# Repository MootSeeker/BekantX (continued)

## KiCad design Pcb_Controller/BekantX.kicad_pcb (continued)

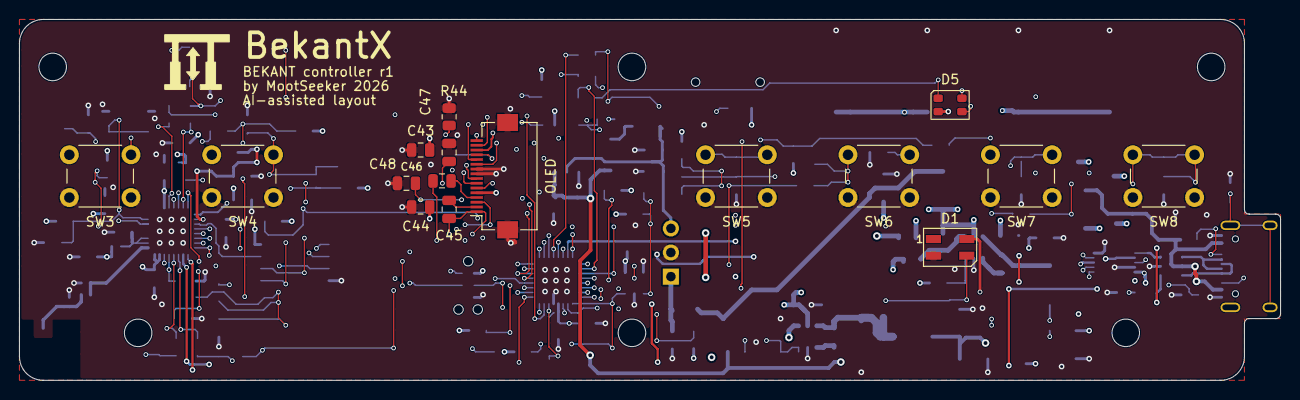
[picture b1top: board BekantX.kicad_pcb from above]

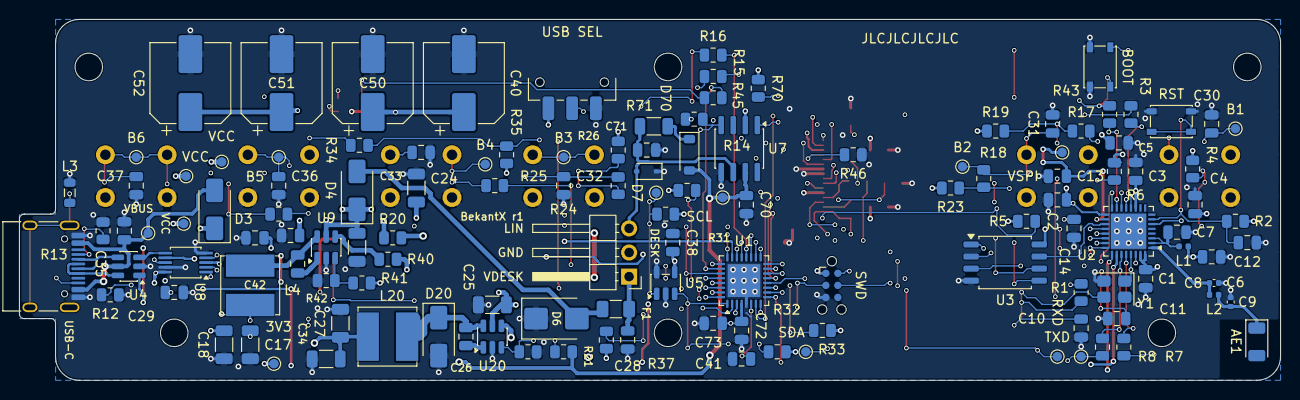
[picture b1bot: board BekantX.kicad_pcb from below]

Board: 6 copper layers, 132.8 x 38.0 mm, 151 parts (129 on the bottom side), 92 nets.

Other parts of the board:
H1, H2, H3, H4, H5, H6: M2.5 hole 2.9 mm; MountingHole_2.9mm_NPTH

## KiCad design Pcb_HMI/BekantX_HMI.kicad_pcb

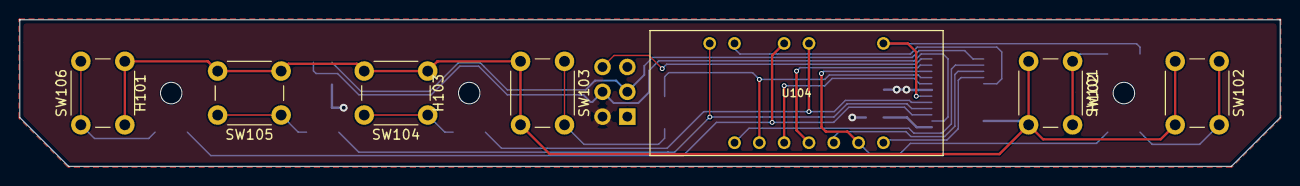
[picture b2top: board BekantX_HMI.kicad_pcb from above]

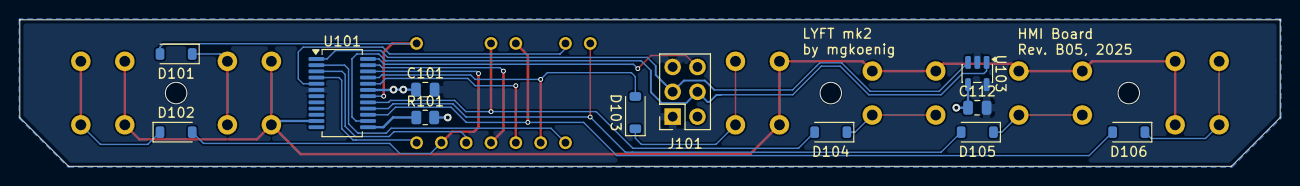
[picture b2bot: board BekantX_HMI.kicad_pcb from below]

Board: 2 copper layers, 129.0 x 15.0 mm, 22 parts (12 on the bottom side), 19 nets.

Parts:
C101: 10u; C_0805_2012Metric
C112: 100n; C_0805_2012Metric
D101, D102, D103, D104, D105, D106: 1N4148W; D_SOD-123
H101, H102, H103: MountingHole; MountingHole_2.2mm_M2
J101: Conn_HMI; PinSocket_2x03_P2.54mm_Vertical
R101: 13k; R_0805_2012Metric
SW101, SW102, SW103, SW104, SW105, SW106: SW_Omron_B3FS; SW_PUSH_6mm
U101: AS1115-BSST; QSOP-24_3.9x8.7mm_P0.635mm
U103: 24FC01T; SOT-23-5
U104: HDSP-433G

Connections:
+3V3: C101.1, C112.1, J101.2, R101.2, U101.19 (VDD), U103.4 (VCC)
GND: C101.2, C112.2, J101.1, J101.5, U101.6 (GND), U103.2 (GND), U103.5 (WP)
HMI_IRQ: J101.6, U101.24 (IRQ)
I2C_SCL: J101.4, U101.14 (SCL), U103.1 (SCL)
I2C_SDA: J101.3, U101.1 (SDA), U103.3 (SDA)
KEY_A: SW101.2, SW102.2, SW103.2, SW104.2, SW105.2, SW106.2, U101.11 (KEYA)
unnamed: D101.1 (K), SW101.1
unnamed: D102.1 (K), SW102.1
unnamed: D103.1 (K), SW103.1
unnamed: D104.1 (K), SW104.1
unnamed: D105.1 (K), SW105.1
unnamed: D106.1 (K), SW106.1
unnamed: R101.1, U101.13 (ISET)
SEG_A: D106.2 (A), U101.15 (SEGA)
SEG_B: D104.2 (A), U101.17 (SEGB)
SEG_DP: D102.2 (A), U101.22 (SEGDP)
SEG_E: D103.2 (A), U101.21 (SEGE)
SEG_F: D105.2 (A), U101.16 (SEGF)
SEG_G: D101.2 (A), U101.18 (SEGG)

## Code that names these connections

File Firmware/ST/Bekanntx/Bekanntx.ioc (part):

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Mcu.Name=STM32G0B1K(B-C-E)Ux
Mcu.Package=UFQFPN32
Mcu.UserName=STM32G0B1KBUx
PA0.Mode=TX_Only_Simplex_Unidirect_Master
PA0.Signal=SPI2_SCK
PA1.GPIOParameters=GPIO_Label
PA1.GPIO_Label=DISP_CS
PA1.Signal=GPIO_Output
PA10.Mode=TX_Only_Simplex_Unidirect_Master
PA10.Signal=SPI2_MOSI
PA11\ [PA9].Mode=Device
PA11\ [PA9].Signal=USB_DM
PA12\ [PA10].Mode=Device
PA12\ [PA10].Signal=USB_DP
PA13.Mode=Serial_Wire
PA13.Signal=SYS_SWDIO
PA14-BOOT0.Mode=Serial_Wire
PA14-BOOT0.Signal=SYS_SWCLK
PA15.Signal=S_TIM2_CH1_ETR
PA2.Mode=Multiprocessor_communication
PA2.Signal=LPUART1_TX
PA3.Mode=Multiprocessor_communication
PA3.Signal=LPUART1_RX
PA4.Mode=NSS_Signal_Hard_Input
PA4.Signal=SPI1_NSS
PA5.Mode=Full_Duplex_Slave
PA5.Signal=SPI1_SCK
PA6.Mode=Full_Duplex_Slave
PA6.Signal=SPI1_MISO
PA7.Mode=Full_Duplex_Slave
PA7.Signal=SPI1_MOSI
PA8.GPIOParameters=GPIO_Label
PA8.GPIO_Label=DISP_DC
PA8.Signal=GPIO_Output
PA9.GPIOParameters=GPIO_Label
PA9.GPIO_Label=DISP_RES
PA9.Signal=GPIO_Output
PB0.GPIOParameters=GPIO_PuPd,GPIO_Label
PB0.GPIO_Label=BTN_2
PB0.GPIO_PuPd=GPIO_PULLUP
PB0.Signal=GPXTI0
PB1.GPIOParameters=GPIO_PuPd,GPIO_Label
PB1.GPIO_Label=BTN_1
PB1.GPIO_PuPd=GPIO_PULLUP
PB1.Signal=GPIO_Input
PB2.GPIOParameters=GPIO_PuPd,GPIO_Label
PB2.GPIO_Label=BTN_3
PB2.GPIO_PuPd=GPIO_PULLUP
PB2.Signal=GPXTI2
PB3.Signal=S_TIM2_CH2
PB4.GPIOParameters=GPIO_PuPd,GPIO_Label
PB4.GPIO_Label=BTN_4
PB4.GPIO_PuPd=GPIO_PULLUP
PB4.Signal=GPIO_Input
PB5.GPIOParameters=PinState,GPIO_Label,GPIO_ModeDefaultOutputPP
PB5.GPIO_Label=FSPI_INT
PB5.GPIO_ModeDefaultOutputPP=GPIO_MODE_OUTPUT_OD
PB5.PinState=GPIO_PIN_SET
PB5.Signal=GPIO_Output
PB6.Mode=LIN
PB6.Signal=USART1_TX
PB7.Mode=LIN
PB7.Signal=USART1_RX
PB8.Mode=I2C
PB8.Signal=I2C1_SCL
PB9.Mode=I2C
PB9.Signal=I2C1_SDA
PC14-OSC32_IN\ (PC14).GPIOParameters=GPIO_PuPd,GPIO_Label
PC14-OSC32_IN\ (PC14).GPIO_Label=BTN_5
PC14-OSC32_IN\ (PC14).GPIO_PuPd=GPIO_PULLUP
PC14-OSC32_IN\ (PC14).Signal=GPIO_Input
PC15-OSC32_OUT\ (PC15).GPIOParameters=GPIO_PuPd,GPIO_Label
PC15-OSC32_OUT\ (PC15).GPIO_Label=BTN_6
PC15-OSC32_OUT\ (PC15).GPIO_PuPd=GPIO_PULLUP
PC15-OSC32_OUT\ (PC15).Signal=GPIO_Input
PC6.Signal=S_TIM2_CH3
RCC.HSE_VALUE=8000000
RCC.SYSCLKFreq_VALUE=16000000
board=custom

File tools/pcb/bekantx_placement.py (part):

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    j10 = fixed(p["J10"], 68.6, 30.0, "B", lambda q: q.box()[2] > q.x + 8, check=False)   # moved below
    j10.put(68.6, 30.0 + (22.0 - min(j10.pad(1)[1], j10.pad(3)[1])), j10.rot)     # pads span y = 22.0 .. 27.08
    pl.keepout("B", (70.2, 20.3, 90.0, 28.8), "J10 housing and cable")
    # input protection directly at the VDESK pin, on the side away from the STM32: fuse, TVS, then D4
    inp = (67.4, 29.2, 82.0, 37.4)
    pl.auto("F1", side="B", near=(70.8, 30.6), radius=3, region=inp)
    pl.auto("C28", side="B", radius=6, region=inp)
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    inflate = lambda b, m: (b[0] - m, b[1] - m, b[2] + m, b[3] + m)

    # ------------------------------------------------------------ 12 V buck (U20) and 3.3 V buck (U9): compact loops first
    a("R22", side="B", radius=6, near={"U2_FB": pin("U20", 3)})              # feedback divider at the FB pin
    a("R21", side="B", radius=6, near={"U2_FB": pin("U20", 3)})
    a("R20", side="B", radius=8)
    # U9 (LMR51610 data sheet 8.4.1): input capacitor as close as possible to VIN/GND, both feedback resistors
    # close to FB. Placed before anything else around U9 (review 2026-11-15, Major 3 and Minor 5).
    a("C15", side="B", near={"VCC": pin("U9", 5), "GND": pin("U9", 2)}, radius=4)
    a("C49", side="B", near={"VCC": pin("U9", 5)}, radius=5)
    a("C16", side="B", radius=6)
    a("R42", side="B", near={"U9_FB": pin("U9", 3)}, radius=5)
    a("R41", side="B", near={"U9_FB": pin("U9", 3)}, radius=5)
    # D4 (VIN -> VCC) between the TVS and the regulators, right of the cable housing
    a("D4", side="B", near={"VIN": (90.5, 24.5), "VCC": (95.0, 24.5)}, radius=6)
    a("C24", side="B", near={"VCC": pin("D4", 1)})
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
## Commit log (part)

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2026-04-16 Add documentation for BekantX project including LIN protocol, requirements, and inter-controller protocol
    - Introduced `bekant-lin-protocol.md` detailing the reverse-engineered LIN protocol for the IKEA BEKANT desk, covering bus characteristics, frame model, node map, runtime payload formats, and known c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
    - Created `description.md` outlining the BekantX requirements specification, including purpose, scope, architectural requirements, functional requirements, safety and fault handling, and non-function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
    - Established `inter-controller-protocol.md` to define the message-level protocol between the primary and secondary controllers, detailing transport definition, fr
2026-04-16 Add initial KiCad project files and .gitignore
2026-04-17 Add KiCad Project
2026-04-17 Update Schematic
2026-04-18 Split Project into two PCBs. HMI PCB now has an OLED Display. Controller PCB is now steered by STM32 uC and uses ESP32-C3 as networking Module with inter CPU protocol.
2026-04-18 Work
2026-04-19 work on HMI
2026-04-22 minor changes - added test points
2026-04-22 Add some Test points
2026-04-22 Add Case
2026-04-22 Add Wi-Fi FTM example for ESP32-C3
    - Created CMakeLists.txt to define project structure.
    - Added main application code in ftm_main.c for FTM (Fine Timing Measurement) functionality.
    - Implemented command-line interface for Wi-Fi station and access point modes, including FTM initiator and responder commands.
    - Introduced configuration options in Kconfig.projbuild for enabling FTM report logging.
    - Added necessary JSON configuration files for Visual Studio Code integration.
    - Updated README.md with detailed usage instructions for the FTM example.
2026-04-23 chore: consolidate code change entries for better organization
2026-04-25 Refactor Wi-Fi FTM example: separate app_main into ftm_app_start and add header file
2026-04-25 feat(led): add WS2812 RGB LED driver with breath animation
    - Add ws2812_transport (C/RMT backend, GPIO18, 10 MHz, GRB order)
    - Add LedDriver C++ class (pixel buffer, brightness scaling, Show/Clear)
    - Add LedAnimator C++ state machine (Blink, FadeIn/Out, FadeInOut, Breath)
    - Add LED_BREATH mode: cubic smooth-step 0->max->0, flicker-free at wrap
    - Add StatusIndicator mapping DeviceStatus to LED patterns
    - Boot pattern: yellow LED_BREATH, period 2 s, brightness 0-100
2026-04-25 feat: enhance application and status indicator classes with detailed documentation and improve configuration paths
2026-04-25 refactor: remove unused core component and clean up application structure
2026-04-25 chore: update .gitignore to exclude all VSCode configuration files
2026-04-30 feat: Add MQTT service for BekantX desk control
    - Introduced MQTT service to manage communication with Home Assistant.
    - Added configuration options for MQTT broker URI, device ID, and topics.
    - Implemented MQTT command handling, state publishing, and auto-discovery for Home Assistant.
    - Integrated deep sleep functionality with configurable wake GPIO.
    - Created necessary classes for handling MQTT credentials, commands, state, and discovery.
    - Updated Kconfig to include new MQTT and deep sleep options.
2026-04-30 feat: Enhance WiFiManager and MQTT service with atomic variables and improved logging
